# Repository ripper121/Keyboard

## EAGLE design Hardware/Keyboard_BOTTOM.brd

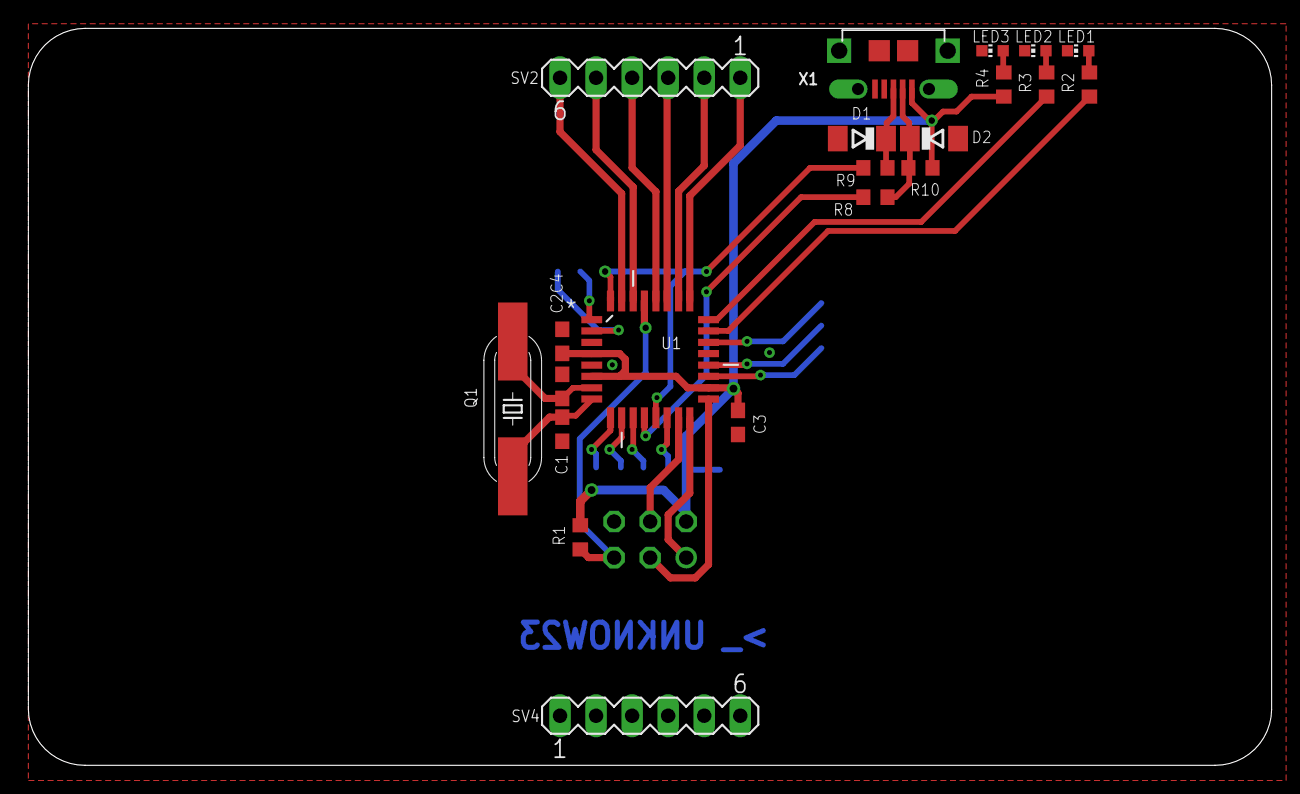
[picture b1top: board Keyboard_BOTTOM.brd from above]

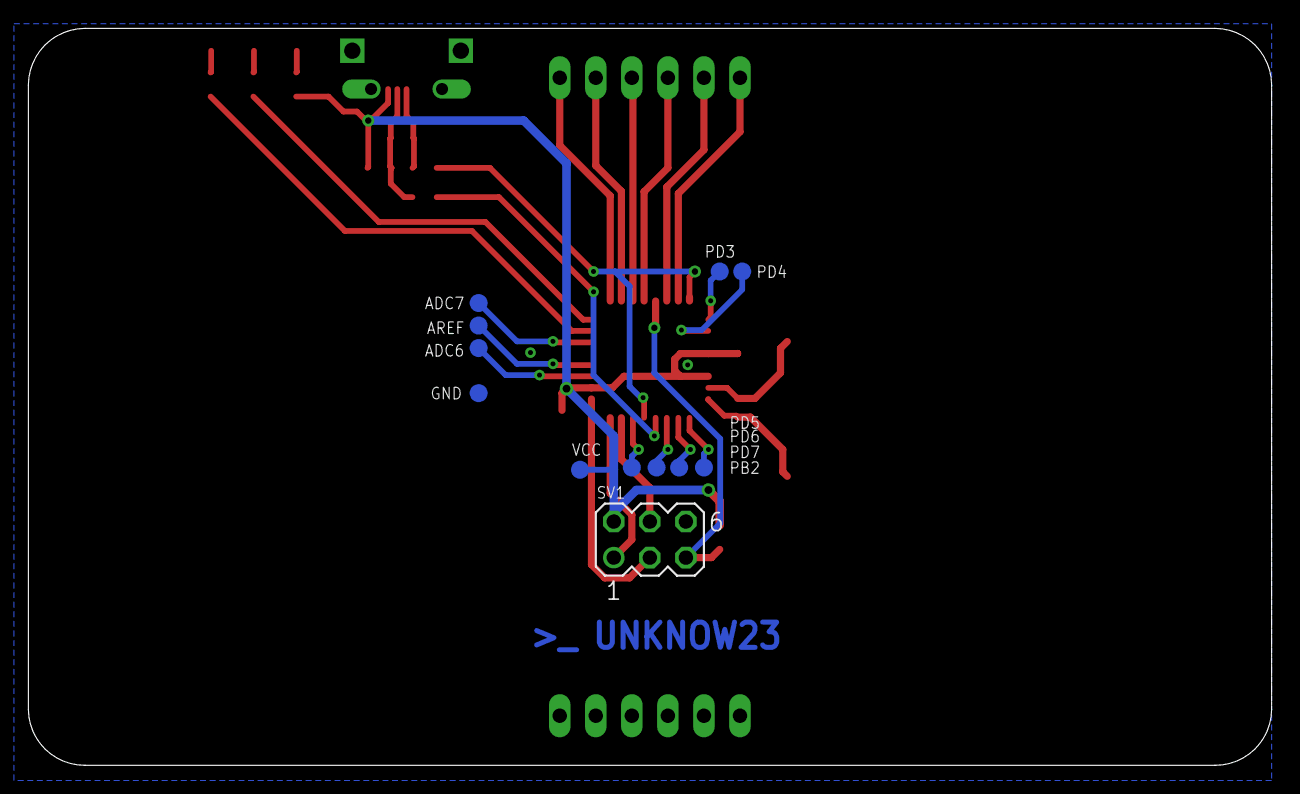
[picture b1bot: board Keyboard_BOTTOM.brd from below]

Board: 2 copper layers, 87.6 x 51.9 mm, 33 parts (12 on the bottom side), 32 nets.

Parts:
ADC6, ADC7: TPB1,27; B1,27
AREF: TPB1,27; B1,27
C1, C2: 22p; C0603
C3: 4.7u; C0603
C4: 100n; C0603
D1, D2: 3V6; SOD80C
GND: TPB1,27; B1,27
LED1, LED2, LED3: CHIP-LED0603
PB2: TPB1,27; B1,27
PD3, PD4, PD5, PD6, PD7: TPB1,27; B1,27
Q1: 12MHz; 11.4X4.5
R1: 10k; R0603
R2, R3, R4: 1k; R0603
R8, R9: 68R; R0603
R10: 2k2; R0603
SV1: MA03-2
SV2, SV4: MA06-1
U1: ATMEGA8A-AU; QFP80P900X900X120-32N
VCC: TPB1,27; B1,27
X1: 4UCONN_20329_V2

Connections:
COL1: SV2.1, U1.25
COL2: SV2.2, U1.26
COL3: SV2.3, U1.27
COL4: SV2.4, U1.28
D+: R9.1, U1.13, U1.32
D-: R8.1, U1.12
GND: C1.2, C2.2, C3.2, C4.2, D1.A, D2.A, GND.TP, LED1.C, LED2.C, LED3.C, SV1.6, SV4.1, SV4.2, SV4.3, SV4.4, SV4.5, SV4.6, U1.3, U1.5, U1.21, X1.BASE@1, X1.BASE@2, X1.GND, X1.SPRT@1, X1.SPRT@2, X1.SPRT@3, X1.SPRT@4
MISO: SV1.1, U1.16
MOSI: SV1.4, U1.15
unnamed: C1.1, Q1.1, U1.8
unnamed: C2.1, Q1.2, U1.7
unnamed: LED3.A, R4.1
unnamed: R3.1, U1.24
unnamed: R2.1, U1.23
unnamed: LED1.A, R2.2
unnamed: LED2.A, R3.2
unnamed: D1.C, R9.2, X1.D+
unnamed: D2.C, R8.2, R10.2, X1.D-
unnamed: PD7.TP, U1.11
unnamed: PD6.TP, U1.10
unnamed: PD5.TP, U1.9
unnamed: PD4.TP, U1.2
unnamed: PD3.TP, U1.1
unnamed: AREF.TP, U1.20
unnamed: ADC7.TP, U1.22
unnamed: ADC6.TP, U1.19
unnamed: PB2.TP, U1.14
RESET: R1.1, SV1.5, U1.29
ROW1: SV2.5, U1.30
ROW2: SV2.6, U1.31
SCK: SV1.3, U1.17
VCC: C3.1, C4.1, R1.2, R4.2, R10.1, SV1.2, U1.4, U1.6, U1.18, VCC.TP, X1.VBUS

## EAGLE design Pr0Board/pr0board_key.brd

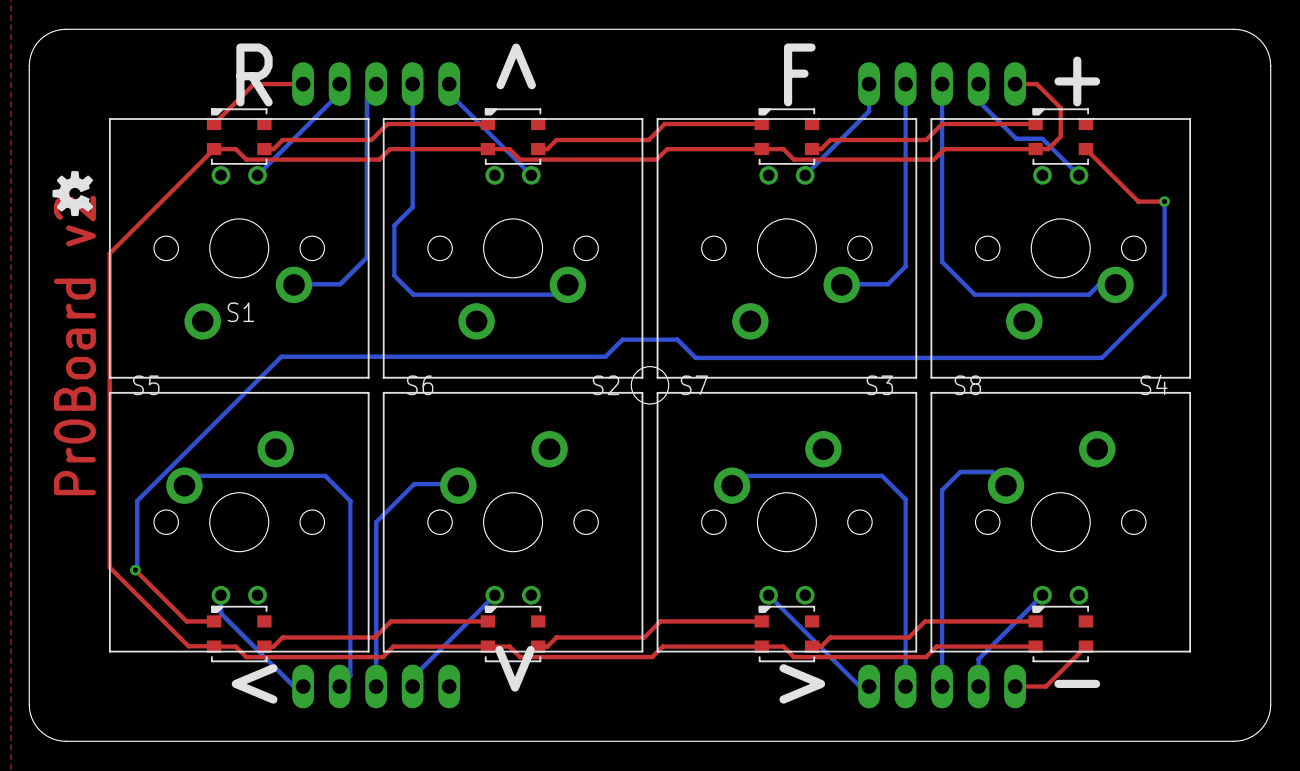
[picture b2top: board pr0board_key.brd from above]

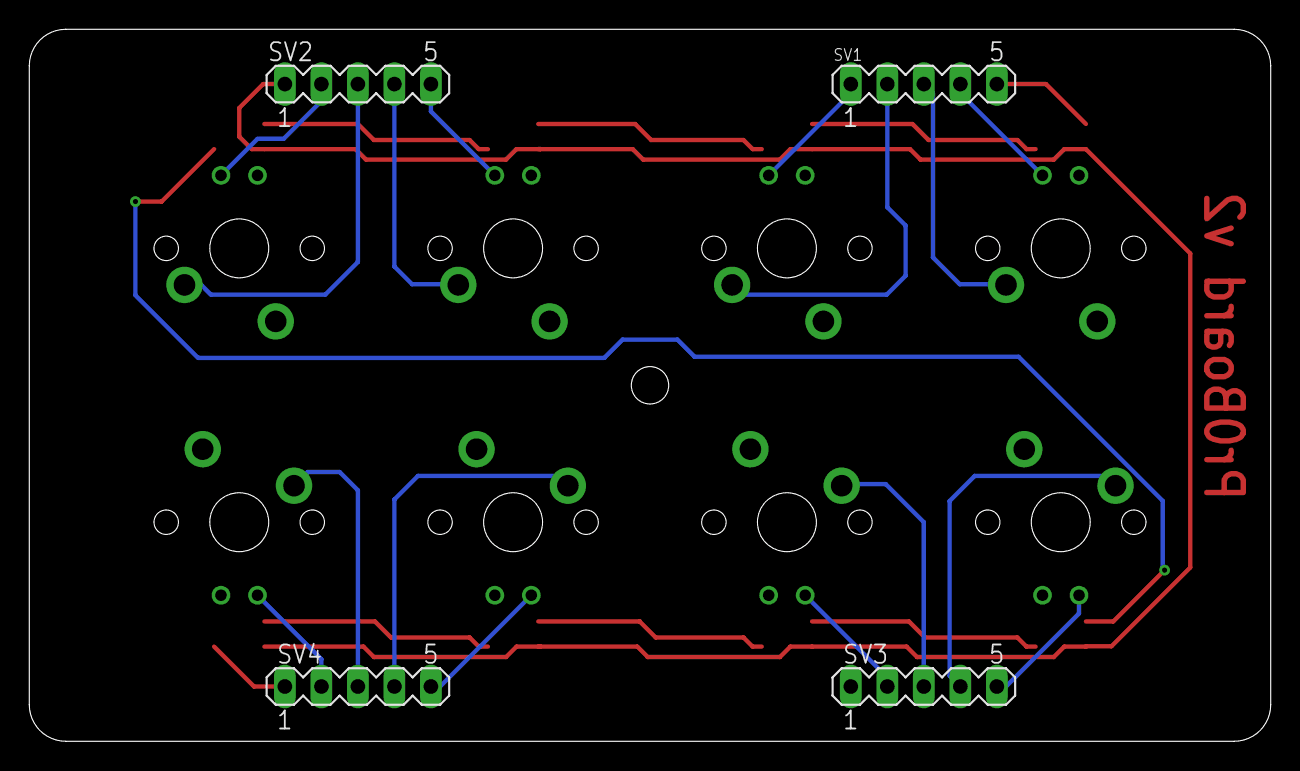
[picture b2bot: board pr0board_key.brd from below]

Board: 2 copper layers, 86.4 x 49.5 mm, 29 parts (4 on the bottom side), 27 nets.

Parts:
LED4, LED5, LED6, LED7, LED8, LED9, LED10, LED11: WS2812B3535; LED3535
M1, M2, M3, M4, M5, M6, M7, M8: DSA_KEYCAP
S1, S2, S3, S4, S5, S6, S7, S8: CPG151101S13 C404353; CHERRY_MX_LED
SV1, SV2, SV3, SV4: MA05-1
U$1: OSHW-LOGOS; OSHW-LOGO-S

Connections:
DIDO: LED7.3, LED8.1
GND: LED4.4, LED5.4, LED6.4, LED7.4, LED8.4, LED9.4, LED10.4, LED11.4, S1.L2, S1.S2, S2.L2, S2.S2, S3.L2, S3.S2, S4.L2, S4.S2, S5.L2, S5.S2, S6.L2, S6.S2, S7.L2, S7.S2, S8.L2, S8.S2, SV3.1
KEY_L_1: S1.L1, SV1.4
KEY_L_2: S2.L1, SV1.1
KEY_L_3: S3.L1, SV2.5
KEY_L_4: S4.L1, SV2.2
KEY_L_5: S5.L1, SV3.5
KEY_L_6: S6.L1, SV3.2
KEY_L_7: S7.L1, SV4.5
KEY_L_8: S8.L1, SV4.2
KEY_S_1: S1.S1, SV1.3
KEY_S_2: S2.S1, SV1.2
KEY_S_3: S3.S1, SV2.4
KEY_S_4: S4.S1, SV2.3
KEY_S_5: S5.S1, SV3.4
KEY_S_6: S6.S1, SV3.3
KEY_S_7: S7.S1, SV4.4
KEY_S_8: S8.S1, SV4.3
unnamed: LED4.3, LED5.1
unnamed: LED5.3, LED6.1
unnamed: LED6.3, LED7.1
unnamed: LED8.3, LED9.1
unnamed: LED9.3, LED10.1
unnamed: LED10.3, LED11.1
WS2812BDI: LED4.1, SV1.5
WS2812BDO: LED11.3, SV4.1
WSVCC: LED4.2, LED5.2, LED6.2, LED7.2, LED8.2, LED9.2, LED10.2, LED11.2, SV2.1

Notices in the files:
parts and their libraries:
crystal-geyer_V1_0: Copyright: Geyer-Electronic
